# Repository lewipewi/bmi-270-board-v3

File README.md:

# BMI270 IMU Node — Board v3

Wearable 6-axis motion node for an IMU gesture controller. Each node samples a
Bosch BMI270 at 200 Hz and streams it over ESP-NOW to a USB receiver on a PC,
where a classifier turns boxing motions into gamepad inputs (Tekken 7 / Steve Fox).
Three identical nodes are worn: left wrist, right wrist, chest.

v3 is a full redesign of v2. v2 was built, debugged through five faults, and
finally found to be **unflashable** (see [What went wrong on v2](#what-went-wrong-on-v2)).
v3's priorities, in order: **(1) flashable, (2) debuggable, (3) charging,
(4) everything else.**

**Status:** layout complete, DRC clean (documented exclusions only), Gerbers
generated and checked, ordered from JLCPCB. Not yet assembled.

---

## At a glance

| | |
|---|---|
| MCU | ESP32-C3-MINI-1-N4 (RISC-V, 4 MB flash, WiFi/BLE, antenna overhangs board edge) |
| IMU | Bosch BMI270, I2C @ 0x68 (CHIP_ID 0x24) |
| Power in | USB-C (5 V) or 1-cell LiPo via JST-PH 2-pin |
| Charging | TP4056, ~255 mA, CHRG status to a GPIO |
| Power path | Schottky + P-FET load sharing (runs from USB when plugged in) |
| Regulator | AP2112K-3.3 LDO, enabled by slide switch |
| Programming | **Native USB** (USB-Serial-JTAG) — no buttons needed; UART header fallback |
| Board | 40.0 × 44.0 × 1.6 mm, **4 layers**, 2 mm corner radii, 2 × M2 holes |
| Assembly | Hand soldered (iron + hot air): 0603 hand-solder passives minimum |

---

## Block diagram / power tree

```
USB-C 5V (VBUS) ── USBLC6 ESD on D+/D−, 5.1k on CC1 and CC2
 ├─► TP4056 charger (R_PROG 4.7k ≈ 255 mA) ──► VBAT ◄── JST-PH battery
 │                                              │
 │                                              └─► Q1 AO3401 P-FET (ON only when USB absent)
 │                                                      │
 └─► D2 MBR0520 Schottky (5 V → ~4.7 V) ───────────────┴──► VSYS (22 µF)
                                                              │
                                        AP2112K-3.3 LDO  (EN ← slide switch, 1M pull-down)
                                                              │
                                                            3V3 ──► ESP32-C3, BMI270,
                                                                    pull-ups, power LED
VBAT ── 1M/1M divider + 100 nF ──► IO0 (battery voltage)
TP4056 CHRG ── 10k pull-up ──► IO1 (charge status)
```

- **USB present:** Q1's gate = VBUS (5 V) > source (VSYS ≈ 4.7 V) → Q1 off; board
  runs from USB through D2; the battery sees only the charger, so charge
  termination works correctly.
- **USB absent:** R5 (100k) pulls Q1's gate to 0 V → Q1 fully on (~50 mΩ); battery
  feeds VSYS. Q1's body diode catches VSYS during the hand-over.
- **Slide switch** only drives the LDO's enable pin — it never carries load current.
  Charging works with the switch OFF; running or flashing needs it ON.
- LDO drops out around a **3.4–3.5 V** battery — firmware should warn/sleep there.

---

## Pin map

| GPIO | Function | Notes |
|---|---|---|
| IO0 | VBAT_SENSE | ADC1_CH0, reads VBAT ÷ 2 |
| IO1 | CHRG | Active low = charging; high = done **or** no USB |
| IO2 | — | Strapping pin, 10k pull-up only |
| IO3 | LED2 | 330 Ω, active high |
| IO4 | BMI270 INT1 | |
| IO5 | I2C SDA | 4.7k pull-up |
| IO6 | I2C SCL | 4.7k pull-up |
| IO7 | BMI270 INT2 | |
| IO8 | — | Strapping pin, **10k pull-up (the v2 fix)** |
| IO9 | BOOT button | Strapping pin, 10k pull-up; usable as a user button after boot |
| IO10 | LED1 | 330 Ω, active high |
| IO18 / IO19 | USB D− / D+ | Native USB |
| IO20 / IO21 | UART0 RX / TX | 1×4 debug header |
| EN | RESET button | 10k + 1 µF |

Power LED (LED3) is hard-wired to 3V3 through 1k.

**Boot straps:** power-up → IO2 = 1, IO8 = 1, IO9 = 1 → boots from flash.
BOOT held → IO9 = 0, IO8 = 1 → download mode. Nothing else can pull a strapping
pin low.

---

## Changes from v2

### Fixes for v2's failures

| v2 | v3 | Why |
|---|---|---|
| **IO8 unconnected** — floated low, so BOOT entered USB_BOOT instead of download mode; board could not be flashed | **10k pull-up on IO8** (and IO2) | Espressif requires IO8 high for the serial bootloader |
| USB D+/D− (IO18/IO19) wired to **two LEDs** | **USB-C D+/D− → IO19/IO18** (native USB); LEDs moved to IO10/IO3 | Flash + console + JTAG over USB with no buttons; deletes the whole CH343P path where most v2 faults lived |
| CH343P USB-serial bridge | **Removed** | Native USB replaces it; 1×4 UART header kept as fallback |
| Rail problems hard to diagnose (D2 fault hid behind a working CH343P) | **12 test points** + power LED | Every measurement that was hard on v2 is now a probe touch |
| CC cold joint made the board "dead" one way up, unprobeable | **CC1 and CC2 test points**, separate 5.1k each | Verify both CC lines directly |
| UART pads under the module, unprobeable | UART on a through-hole header + test points | |
| One pin of each tactile switch pair used | **Both pins of each pair connected** | A single cold joint is no longer fatal |
| EN RC: 10k + 100 nF | **10k + 1 µF** | Espressif C3 hardware guideline |

### New features

| Feature | Details |
|---|---|
| Battery charging | TP4056, 4.7k PROG (~255 mA = 0.5C for ~500 mAh), TEMP tied to GND, CHRG → IO1 |
| Load sharing | D2 Schottky from VBUS + AO3401 P-FET from battery (drain = VBAT, source = VSYS, gate = VBUS with 100k pull-down) |
| Slide switch moved | v2: selected VBAT **or** VBUS as LDO input (in the power path). v3: on the LDO **enable** pin only, with 1M pull-down for mid-slide |
| Battery sense | 1M/1M on **VBAT** (1.9 µA) — v2 used 100k/100k (19 µA) on the switched rail |
| BMI270 INT2 | Connected (IO7) — separates FIFO watermark from data-ready |
| BMI270 unused pins | ASDx/ASCx → VDDIO, OCSB/OSDO no-connect, per Bosch datasheet Table 22. (v2 left all four floating; an earlier plan to ground all four would have violated Table 22.) |
| Power LED | On 3V3 — instant "is the rail up?" |
| Battery protection | Relies on the pack's own protection board (DW01A/FS8205 not on the PCB) |

### Pin map, v2 → v3

| Signal | v2 | v3 |
|---|---|---|
| SDA / SCL | IO5 / IO6 | IO5 / IO6 |
| INT1 | IO4 | IO4 |
| INT2 | not connected | IO7 |
| VBAT sense | IO0 (unconfirmed) | IO0 |
| LEDs | IO19 / IO18 (USB pins!) | IO10 / IO3 |
| USB D+ / D− | LEDs | IO19 / IO18 |
| CHRG | — | IO1 |
| IO8 | **floating** | 10k pull-up |
| IO2 | free | 10k pull-up |
| UART0 | → CH343P | → 1×4 header |

### Layout changes

| | v2 | v3 |
|---|---|---|
| Layers | 2 | **4**: L1 signals + GND pour / L2 solid GND / L3 +3V3 plane with VBUS island / L4 signals + GND pour |
| Stitching | — | 121 GND vias, ground pours tied down across the board |
| USB pair | — | 0.3 mm / 0.21 mm gap, ≈ 90 Ω differential, 27.8 / 27.4 mm, top layer only over solid GND, no vias |
| Module grounding | — | Via in each of the 9 centre GND pads |
| TP4056 | — | 6 thermal vias in the exposed pad |
| Footprints | — | Hand-solder variants; 10 µF in 0805, 22 µF in 1206 for DC-bias derating |
| Mechanical | — | IMU at board centre, away from charger/LDO/holes/edges; antenna overhang, plastic-only keep-out |

---

## Bill of materials (key parts)

| Ref | Part | Notes |
|---|---|---|
| U4 | ESP32-C3-MINI-1-N4 | |
| U5 | BMI270 | LGA-14 — hardest part to hand solder |
| U2 | TP4056 (ESOP-8) | |
| U1 | AP2112K-3.3 (Tech Public) | Clone — check dropout |
| Q1 | AO3401 P-FET | Verify P-channel with a meter before fitting |
| D2 | MBR0520LT1G | |
| D1 | USBLC6-2SC6 | |
| USB1 | USB-C 16-pin (TYPE-C 16PIN 2MD(073)) | Locating pegs set to NPTH |
| J1 | JST-PH 2-pin, vertical (B2B-PH-K-S) | Check pin 1 (+) against the battery lead |
| J2 | 1×4 2.54 mm right-angle header | 3V3 / GND / TX / RX (3V3 is a reference, not an input) |
| SW1, SW2 | TS-1187A tactile | RESET, BOOT |
| SW3 | SS-12D00-G3 slide switch | Power (LDO enable). No 3D model |

Resistors 0603: R1/R2 5.1k (CC), R3 10k (CHRG pull-up), R4 4.7k (PROG), R5 100k
(Q1 gate), R6/R7 1M (VBAT divider), R8 10k (EN), R9/R10/R11 10k (IO2/IO9/IO8),
R12/R13 330 (LEDs), R14 1M (LDO EN pull-down), R15 1k (power LED), R16/R17 4.7k (I2C).
Capacitors: C1 10 µF (VBUS), C2 10 µF (VBAT), C3 22 µF (VSYS), C4 10 µF (LDO out),
C5 1 µF (LDO in), C6 100 nF (VBAT sense), C7 10 µF + C8 100 nF (module),
C9 1 µF (EN), C10/C11 100 nF (BMI270 VDD/VDDIO). Use ≥ 10 V rating on 10/22 µF.

---

## Fabrication

- JLCPCB, 4 layers, 1.6 mm, stackup **JLC04161H-7628**, HASL (with lead), tented vias.
- Gerbers: KiCad 9, Protel extensions, 4.6 mm, X2 off, subtract mask from silk.
- Drill: Excellon, mm, decimal, PTH/NPTH separate, oval holes in route mode
  (the four USB-C shell tabs are slots).
- Documented DRC exclusions: USB-C peg-hole clearance (footprint geometry, NPTH),
  module pads 11 and 51 single thermal spoke (module GND tied internally).

---

## Bring-up checklist

Populate and test in stages so faults show up one at a time.

1. **Bare board:** no short from 3V3, VBUS, VSYS, VBAT to GND.
2. **USB-C, ESD, CC resistors, D2:** VBUS = 5 V **with the cable both ways up**;
   VSYS ≈ 4.7 V.
3. **LDO, its caps, slide switch, power LED:** switch ON → 3V3 = 3.3 V, LED lit.
4. **Module + boot parts:** appears as a COM port with no buttons pressed; flash blink.
   PlatformIO needs `-DARDUINO_USB_MODE=1 -DARDUINO_USB_CDC_ON_BOOT=1` or `Serial`
   goes to the UART header.
5. **BMI270 + pull-ups:** I2C scan finds 0x68, CHIP_ID reads 0x24. If not, probe
   SDA/SCL test points.
6. **Battery + charger:** check battery polarity with a meter first; CHRG low while
   charging; board keeps running when USB is unplugged.

If native USB stops working: hold BOOT, tap RESET, release BOOT, upload.
Last resort: UART header with a spare ESP32 dev board as the adapter.

---

## Known limitations

- **CHRG can't distinguish "charge done" from "no USB"** — only one status pin;
  combine with the VBAT reading.
- **No reverse-polarity protection on the battery.** Check every new cell's
  polarity before plugging in.
- VBUS sees ~33 µF at plug-in (USB 2.0 limit is 10 µF) — common on dev boards,
  fine in practice.
- USB 500 mA budget is slightly exceeded with charging + WiFi TX peaks — fine on a
  USB-C laptop port.
- The BMI270 is rotated 180° on the board; define the body frame in firmware.
- STEP export: the ESP32 module and USB-C 3D models are offset from their real
  (footprint) positions by ~2.7 mm and ~1.2 mm. Use footprint dimensions for
  enclosure design.

---

## What went wrong on v2

Kept here because it explains most of v3's decisions.

1. **Pre-power checks passed** (VBAT–GND = 196 kΩ confirmed the sense divider).
2. **USB-C CC cold joint** — board dead one way up; fixed by flipping the cable.
   Lesson: a C-to-C source gives 0 V until CC negotiation succeeds, and the CC pins
   can't be probed under the connector.
3. **D2 not conducting** (5.31 V in, 0.63 V out) — reworked. Masked by the CH343P
   enumerating fine from upstream of D2.
4. **No UART output** — cold joints on the module castellations; resoldered.
   Boot log then showed a correct blank-chip loop (`invalid header: 0xffffffff`).
5. **Could not enter download mode** — holding BOOT gave `boot:0x0 (USB_BOOT)`
   because IO8 floated low, and USB went to LEDs. v2 abandoned.

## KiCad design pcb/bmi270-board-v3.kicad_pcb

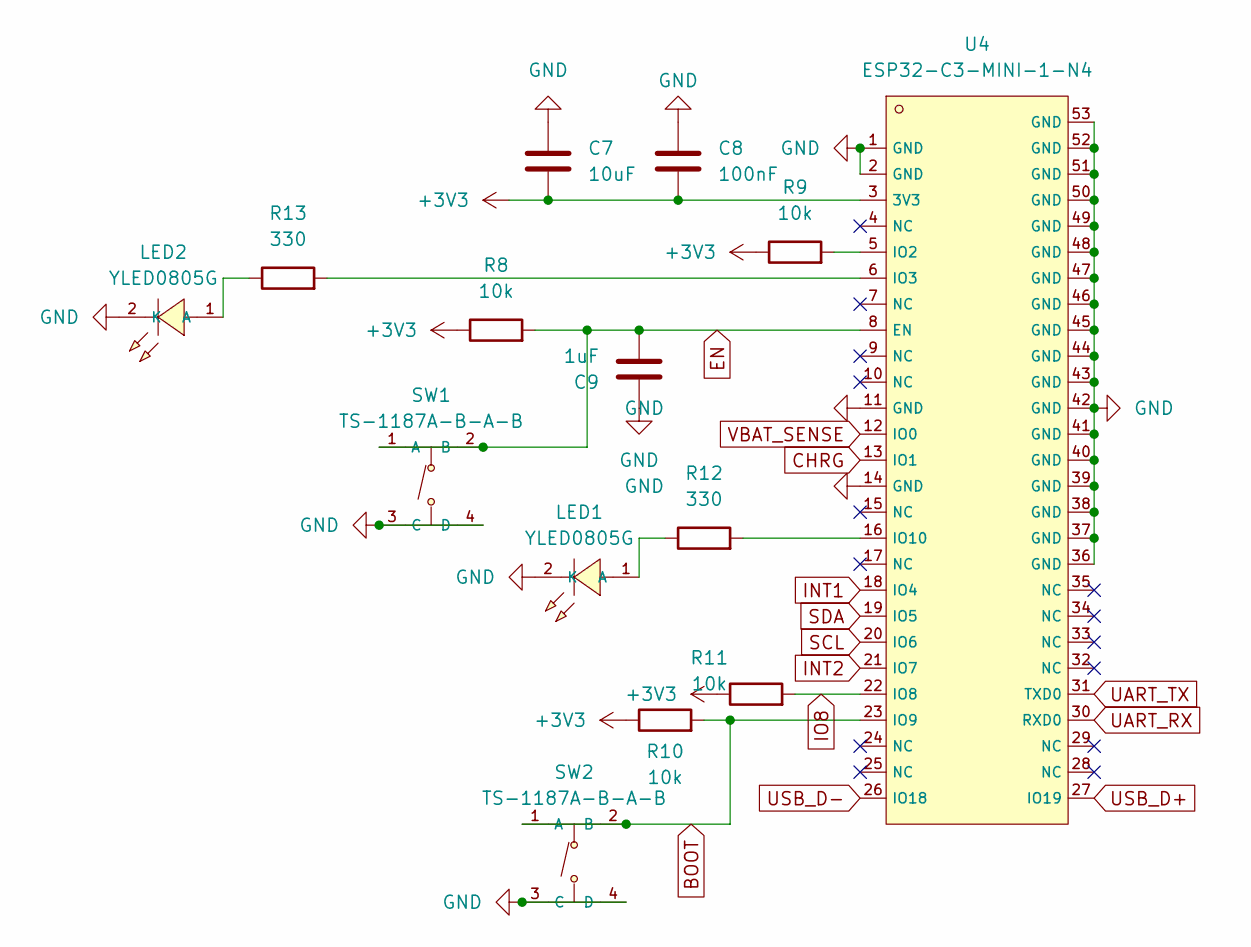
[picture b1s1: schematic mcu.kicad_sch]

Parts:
C7: 10uF; C_0805_2012Metric_Pad1.18x1.45mm_HandSolder
C8: 100nF; C_0603_1608Metric_Pad1.08x0.95mm_HandSolder
C9: 1uF; C_0603_1608Metric_Pad1.08x0.95mm_HandSolder
LED1, LED2: YLED0805G; C25170728_LED0805-FD-GREEN; LCSC C25170728
R8, R9, R10, R11: 10k; R_0603_1608Metric_Pad0.98x0.95mm_HandSolder
R12, R13: 330; R_0603_1608Metric_Pad0.98x0.95mm_HandSolder
SW1, SW2: TS-1187A-B-A-B; C318884_SW-SMD_4P-L5_1-W5_1-P3_70-LS6_5-TL_H1_5; LCSC C318884
U4: ESP32-C3-MINI-1-N4; C2838502_WIFIM-SMD_ESP32-C3-MINI-1; LCSC C2838502

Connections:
+3V3: C7.2, C8.2, R8.1, R9.1, R10.1, R11.1, U4.3 (3V3); also elsewhere on the board
BOOT: R10.2, SW2.1 (A), SW2.2 (B), U4.23 (IO9); also elsewhere on the board
CHRG: U4.13 (IO1); also elsewhere on the board
EN: C9.2, R8.2, SW1.1 (A), SW1.2 (B), U4.8 (EN); also elsewhere on the board
GND: C7.1, C8.1, C9.1, LED1.2 (K), LED2.2 (K), SW1.3 (C), SW1.4 (D), SW2.3 (C), SW2.4 (D), U4.1 (GND), U4.2 (GND), U4.11 (GND), U4.14 (GND), U4.36 (GND), U4.37 (GND), U4.38 (GND), U4.39 (GND), U4.40 (GND), U4.41 (GND), U4.42 (GND), U4.43 (GND), U4.44 (GND), U4.45 (GND), U4.46 (GND), U4.47 (GND), U4.48 (GND), U4.49 (GND), U4.50 (GND), U4.51 (GND), U4.52 (GND), U4.53 (GND); also elsewhere on the board
INT1: U4.18 (IO4); also elsewhere on the board
INT2: U4.21 (IO7); also elsewhere on the board
IO8: R11.2, U4.22 (IO8); also elsewhere on the board
unnamed: LED1.1 (A), R12.1
unnamed: LED2.1 (A), R13.1
unnamed: R9.2, U4.5 (IO2)
unnamed: R13.2, U4.6 (IO3)
unnamed: R12.2, U4.16 (IO10)
SCL: U4.20 (IO6); also elsewhere on the board
SDA: U4.19 (IO5); also elsewhere on the board
UART_RX: U4.30 (RXD0); also elsewhere on the board
UART_TX: U4.31 (TXD0); also elsewhere on the board
USB_D+: U4.27 (IO19); also elsewhere on the board
USB_D-: U4.26 (IO18); also elsewhere on the board
VBAT_SENSE: U4.12 (IO0); also elsewhere on the board

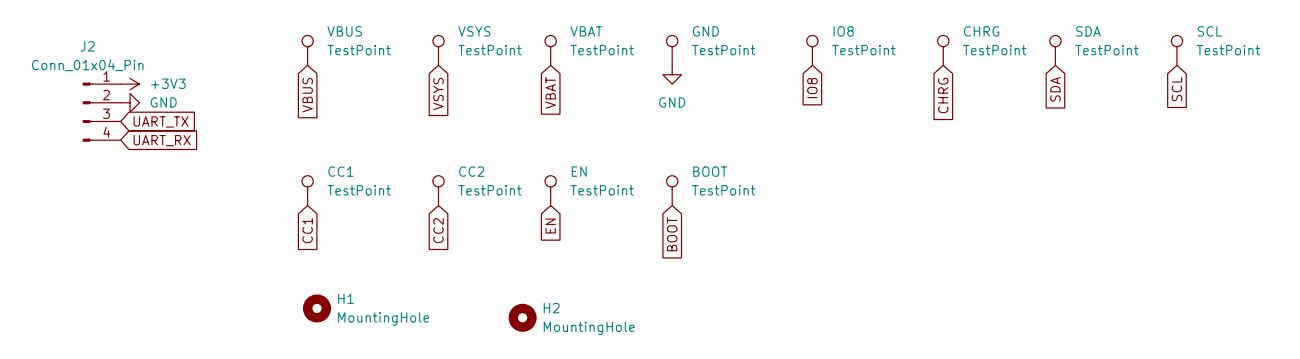
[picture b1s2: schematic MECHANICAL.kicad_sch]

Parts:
BOOT: TestPoint; TestPoint_Pad_D1.0mm
CC1, CC2: TestPoint; TestPoint_Pad_D1.0mm
CHRG: TestPoint; TestPoint_Pad_D1.0mm
EN: TestPoint; TestPoint_Pad_D1.0mm
GND: TestPoint; TestPoint_Pad_D1.0mm
H1, H2: MountingHole; MountingHole_2.2mm_M2
IO8: TestPoint; TestPoint_Pad_D1.0mm
J2: Conn_01x04_Pin; PinHeader_1x04_P2.54mm_Vertical
SCL: TestPoint; TestPoint_Pad_D1.0mm
SDA: TestPoint; TestPoint_Pad_D1.0mm
VBAT: TestPoint; TestPoint_Pad_D1.0mm
VBUS: TestPoint; TestPoint_Pad_D1.0mm
VSYS: TestPoint; TestPoint_Pad_D1.0mm

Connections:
+3V3: J2.1; also elsewhere on the board
BOOT: BOOT.1; also elsewhere on the board
CC1: CC1.1; also elsewhere on the board
CC2: CC2.1; also elsewhere on the board
CHRG: CHRG.1; also elsewhere on the board
EN: EN.1; also elsewhere on the board
GND: GND.1, J2.2; also elsewhere on the board
IO8: IO8.1; also elsewhere on the board
SCL: SCL.1; also elsewhere on the board
SDA: SDA.1; also elsewhere on the board
UART_RX: J2.4; also elsewhere on the board
UART_TX: J2.3; also elsewhere on the board
VBAT: VBAT.1; also elsewhere on the board
VBUS: VBUS.1; also elsewhere on the board
VSYS: VSYS.1; also elsewhere on the board

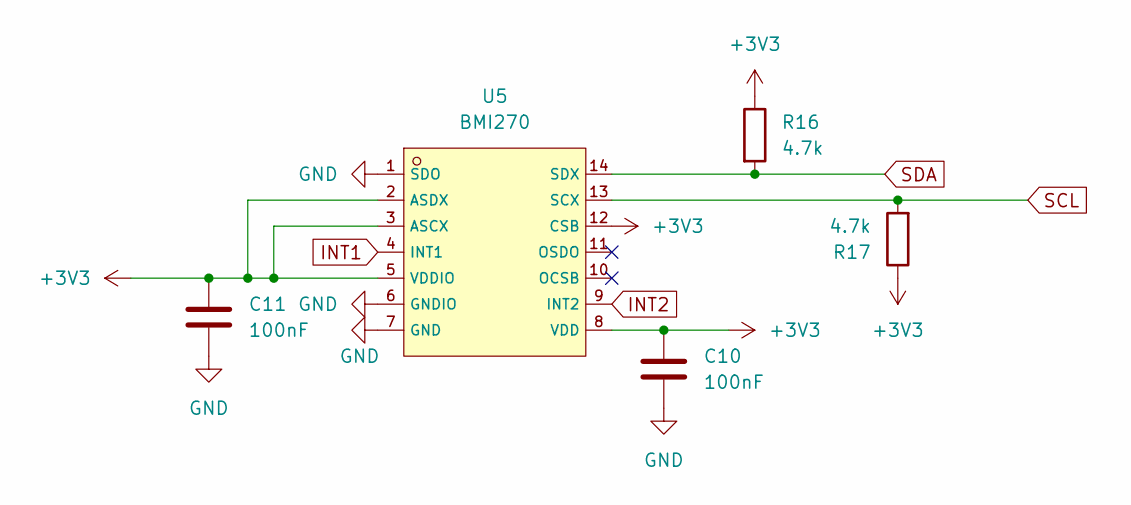
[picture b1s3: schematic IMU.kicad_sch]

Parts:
C10, C11: 100nF; C_0603_1608Metric_Pad1.08x0.95mm_HandSolder
R16, R17: 4.7k; R_0603_1608Metric_Pad0.98x0.95mm_HandSolder
U5: BMI270; C2836813_LGA-14_L3_0-W2_5-P0_50-BR; LCSC C2836813

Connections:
+3V3: C10.1, C11.1, R16.1, R17.1, U5.2 (ASDX), U5.3 (ASCX), U5.5 (VDDIO), U5.8 (VDD), U5.12 (CSB); also elsewhere on the board
GND: C10.2, C11.2, U5.1 (SDO), U5.6 (GNDIO), U5.7 (GND); also elsewhere on the board
INT1: U5.4 (INT1); also elsewhere on the board
INT2: U5.9 (INT2); also elsewhere on the board
SCL: R17.2, U5.13 (SCX); also elsewhere on the board
SDA: R16.2, U5.14 (SDX); also elsewhere on the board

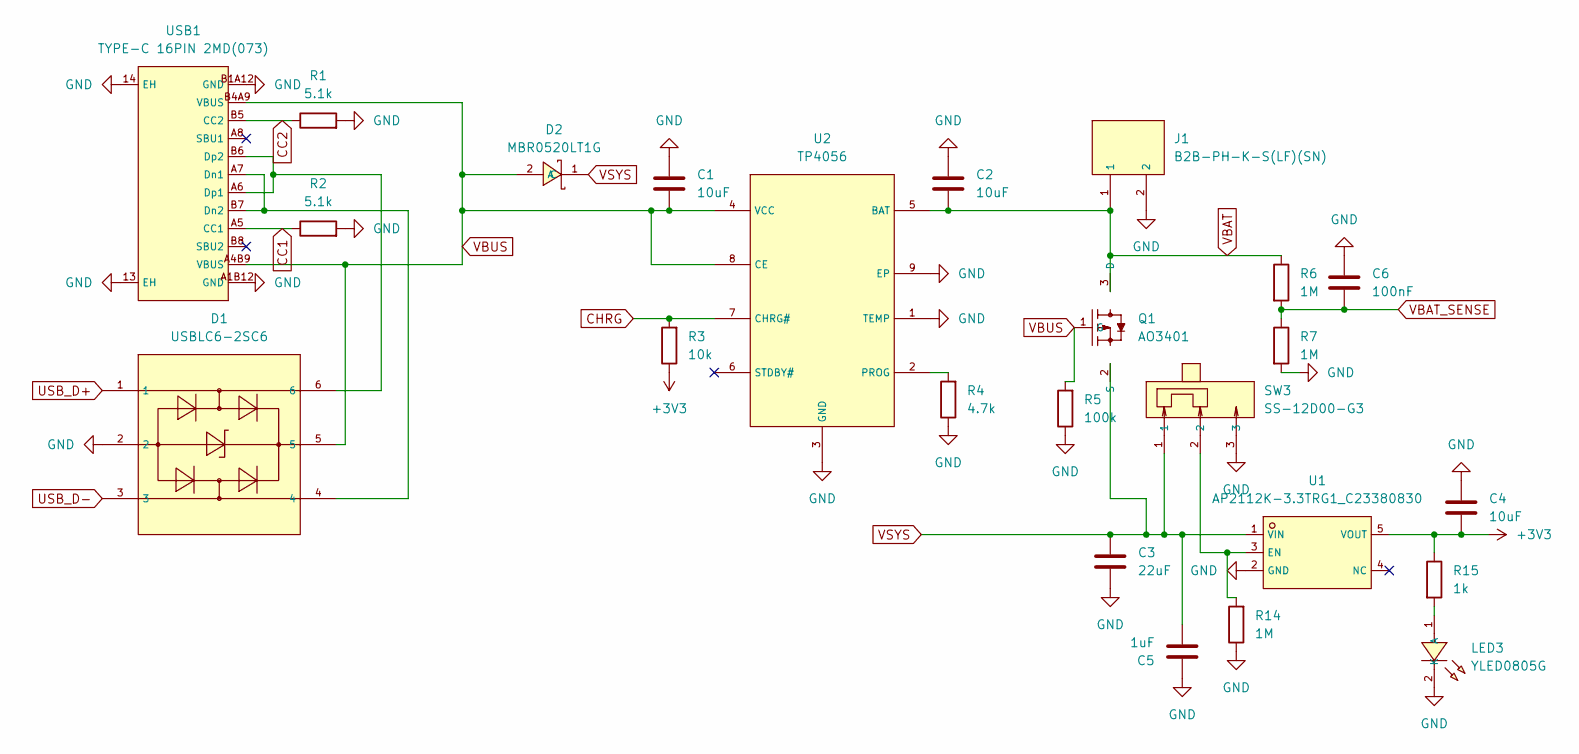
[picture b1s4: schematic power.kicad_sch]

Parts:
C1, C2, C4: 10uF; C_0805_2012Metric_Pad1.18x1.45mm_HandSolder
C3: 22uF; C_1206_3216Metric_Pad1.33x1.80mm_HandSolder
C5: 1uF; C_0603_1608Metric_Pad1.08x0.95mm_HandSolder
C6: 100nF; C_0603_1608Metric_Pad1.08x0.95mm_HandSolder
D1: USBLC6-2SC6; C7519_SOT-23-6_L2_9-W1_6-P0_95-LS2_8-BL; LCSC C7519
D2: MBR0520LT1G; C23848_SOD-123_L2_8-W1_8-LS3_7-RD; LCSC C23848
J1: B2B-PH-K-S(LF)(SN); C131337_CONN-TH_B2B-PH-K-S; LCSC C131337
LED3: YLED0805G; C25170728_LED0805-FD-GREEN; LCSC C25170728
Q1: AO3401; C181091_SOT-23-3_L2_9-W1_3-P1_90-LS2_4-BR; LCSC C181091
R1, R2: 5.1k; R_0603_1608Metric_Pad0.98x0.95mm_HandSolder
R3: 10k; R_0603_1608Metric_Pad0.98x0.95mm_HandSolder
R4: 4.7k; R_0603_1608Metric_Pad0.98x0.95mm_HandSolder
R5: 100k; R_0603_1608Metric_Pad0.98x0.95mm_HandSolder
R6, R7, R14: 1M; R_0603_1608Metric_Pad0.98x0.95mm_HandSolder
R15: 1k; R_0603_1608Metric_Pad0.98x0.95mm_HandSolder
SW3: SS-12D00-G3; C22355741_SW-TH_3P-L8_8-W3_9-P2_50_SS12D00G3; LCSC C22355741
U1: AP2112K-3.3TRG1_C23380830; C23380830_SOT-23-5_L2_9-W1_6-P0_95-LS2_8-BR; LCSC C23380830
U2: TP4056; C16581_ESOP-8_L4_9-W3_9-P1_27-LS6_0-BL-EP; LCSC C16581
USB1: TYPE-C 16PIN 2MD(073); C2765186_USB-C-SMD_TYPE-C-16PIN-2MD-073; LCSC C2765186

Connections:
+3V3: C4.2, R3.1, R15.1, U1.5 (VOUT); also elsewhere on the board
CC1: R2.1, USB1.A5 (CC1); also elsewhere on the board
CC2: R1.1, USB1.B5 (CC2); also elsewhere on the board
CHRG: R3.2, U2.7 (CHRG#); also elsewhere on the board
GND: C1.1, C2.1, C3.2, C4.1, C5.1, C6.1, D1.2, J1.2, LED3.2 (K), R1.2, R2.2, R4.1, R5.1, R7.2, R14.1, SW3.3, U1.2 (GND), U2.1 (TEMP), U2.3 (GND), U2.9 (EP), USB1.13 (EH), USB1.14 (EH), USB1.A1B12 (GND), USB1.B1A12 (GND); also elsewhere on the board
unnamed: LED3.1 (A), R15.2
unnamed: R14.2, SW3.2, U1.3 (EN)
unnamed: R4.2, U2.2 (PROG)
unnamed: D1.4, USB1.A7 (Dn1), USB1.B7 (Dn2)
unnamed: D1.6, USB1.A6 (Dp1), USB1.B6 (Dp2)
USB_D+: D1.1; also elsewhere on the board
USB_D-: D1.3; also elsewhere on the board
VBAT: C2.2, J1.1, Q1.3 (D), R6.1, U2.5 (BAT); also elsewhere on the board
VBAT_SENSE: C6.2, R6.2, R7.1; also elsewhere on the board
VBUS: C1.2, D1.5, D2.2 (A), Q1.1 (G), R5.2, U2.4 (VCC), U2.8 (CE), USB1.A4B9 (VBUS), USB1.B4A9 (VBUS); also elsewhere on the board
VSYS: C3.1, C5.2, D2.1 (C), Q1.2 (S), SW3.1, U1.1 (VIN); also elsewhere on the board

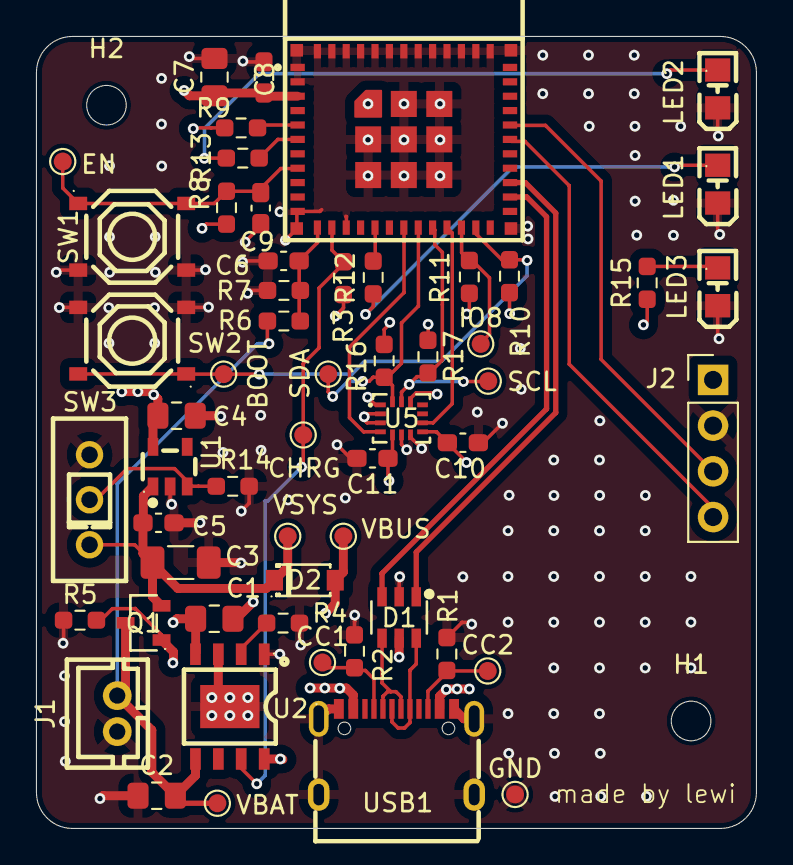
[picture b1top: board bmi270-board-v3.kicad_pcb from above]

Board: 4 copper layers, 40.0 x 44.0 mm, 58 parts (0 on the bottom side), 30 nets.
